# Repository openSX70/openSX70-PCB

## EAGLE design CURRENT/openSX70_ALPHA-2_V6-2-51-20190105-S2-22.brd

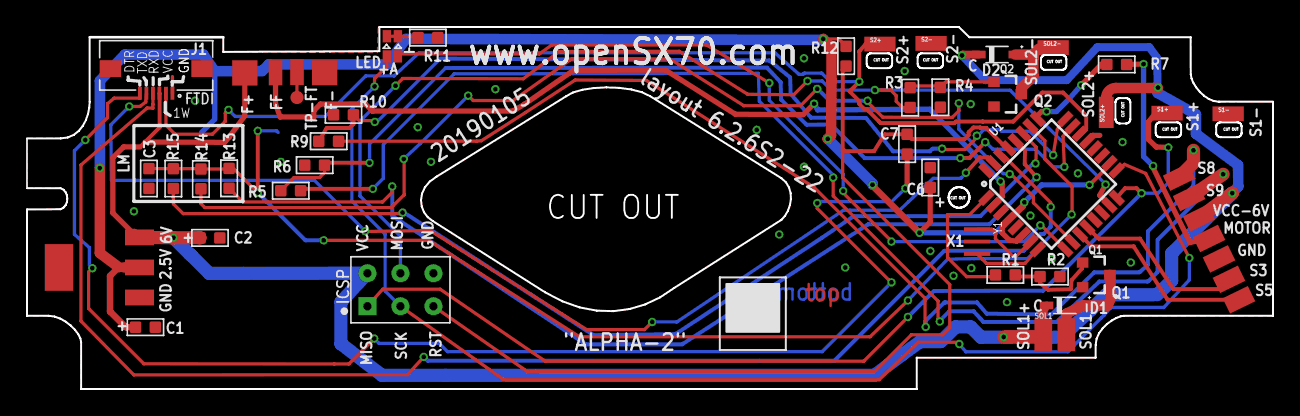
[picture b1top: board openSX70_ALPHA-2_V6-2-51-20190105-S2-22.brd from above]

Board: 2 copper layers, 95.9 x 27.9 mm, 40 parts (1 on the bottom side), 34 nets.

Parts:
C1: 10uf; C0603
C2, C3, C6, C7: 100nf; C0603
D1, D2: 1N4148WSF; SODFL2512X100N
D3: VBPW34S; SOD6439X130N
ICSP: ICSP; H2X3-2.54
J1: 687106183722
LD11172.5V: LD1117 2.5V; SOT223
Q1, Q2: 5.8A/30V/35mΩ; SOT23-3
R1, R3, R7, R14: 100R; R0603
R2, R4, R15: 100K 1/10W; R0603
R5, R9, R13: 15K 1/10W; R0603
R6, R10, R12: 10K; R0603
R11: 1K 1/10W; R0603
S1+, S1-, S2+, S2-: SX70-S-PAD-NEW; SX70-S-PAD2
SOL1: SX70-SOLENOID1-2PADS; SX70-SOLENOID1-2
SOL2+, SOL2-: SX70-S-PAD-NEW; SX70-S-PAD2
TP1: TEST-POINT3X4; PAD.03X.04
U1: ATMEGA328P_TQFP; TQFP32-08
U$1: SX70-7-PAD; SX70-7-PAD-PROPER
U$2: FFA; FFA-PAD-PACKAGE
U$4: LTST-C195KGJRKT; LTST-BILED-15X16
Y1: CSTCE8M00G52Z-R0; CFP95P160X100-3N

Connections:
3.3V: C1.2, C6.1, D3.C, LD11172.5V.2, R12.2, U1.4, U1.6, U1.18
6V: C2.2, D1.C, D2.C, ICSP.6, J1.3, LD11172.5V.3, SOL1.SOL1+, SOL2+.P$1, U$1.VCC, U$2.F+
DTR: C7.1, J1.6
FF: U1.2, U$2.FF
GND: C1.1, C2.1, C3.2, C6.2, ICSP.4, J1.1, LD11172.5V.1, Q1.2, Q2.2, R2.1, R4.1, R6.2, R10.2, R11.1, S1-.P$1, S2-.P$1, U1.3, U1.5, U1.21, U$1.GND, U$2.F-, Y1.GND
LED: ICSP.2, U1.17, U$4.P$1
LED2: U1.9, U$4.P$2
MOTOR+: R7.1, U1.25
MOTOR-HEADER: R7.2, U$1.MOTOR
unnamed: Q1.1, R1.2, R2.2
unnamed: R11.2, U$4.P$3, U$4.P$4
unnamed: Q2.1, R3.2, R4.2
unnamed: U1.7, Y1.IN
unnamed: TP1.P$1, U$2.FT
unnamed: U1.8, Y1.OUT
PDIODE: C3.1, D3.A, R13.2, R14.1, R15.1, U1.26
RST: C7.2, ICSP.3, R12.1, U1.29
RXD: J1.4, U1.30
S1: ICSP.1, S1+.P$1, U1.16
S2: J1.2, S2+.P$1, U1.22
S3: U1.12, U$1.S3
S5: U1.11, U$1.S5
S8@2.5V: R9.2, R10.1, U1.24
S8@6V: R9.1, U$1.S8
S9@2.5V: R5.2, R6.1, U1.23
S9@6V: R5.1, U$1.S9
SOL1: R1.1, U1.1
SOL1-: D1.A, Q1.3, SOL1.SOL1-
SOL2: ICSP.5, R3.1, U1.15
SOL2-: D2.A, Q2.3, SOL2-.P$1
TXD: J1.5, U1.31
V1: R14.2, U1.10
V2-SDA: R15.2, U1.27
V3-SCL: R13.1, U1.28

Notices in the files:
CURRENT/openSX70_ALPHA-2_V6-2-51-20190105-S2-22.brd:
Creative Commons "Attribution-NonCommercial 4.0 International (CC BY-NC 4.0)"
https://creativecommons.org/licenses/by-nc/4.0
parts and their libraries:
SparkFun-Connectors: Licensing: Creative Commons ShareAlike 4.0 International - https://creativecommons.org/licenses/by-sa/4.0
